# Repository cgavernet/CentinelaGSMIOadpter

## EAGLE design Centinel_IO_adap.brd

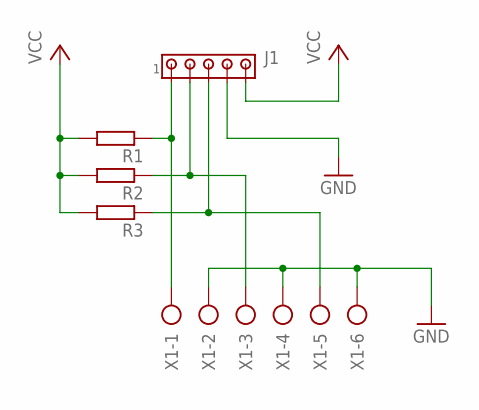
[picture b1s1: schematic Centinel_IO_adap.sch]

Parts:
J1: MTA05-156; 1X5MTA
R1, R2, R3: R-EU_0207/7; 0207/7
X1: AK500/6

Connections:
GND: J1.4, X1.2, X1.4, X1.6
unnamed: J1.1, R1.1, X1.1
unnamed: J1.2, R2.1, X1.3
unnamed: J1.3, R3.1, X1.5
VCC: J1.5, R1.2, R2.2, R3.2

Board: 2 copper layers, 5 parts (0 on the bottom side), 5 nets, no tracks yet.

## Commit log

2020-05-04 inicial
